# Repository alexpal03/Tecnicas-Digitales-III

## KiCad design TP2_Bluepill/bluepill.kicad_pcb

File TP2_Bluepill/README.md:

# TODO

* CRC              [listo]
* Recepcion RS485  [listo]
* Urgente: BMP280  []
* Urgente: PWM 10KHz  []

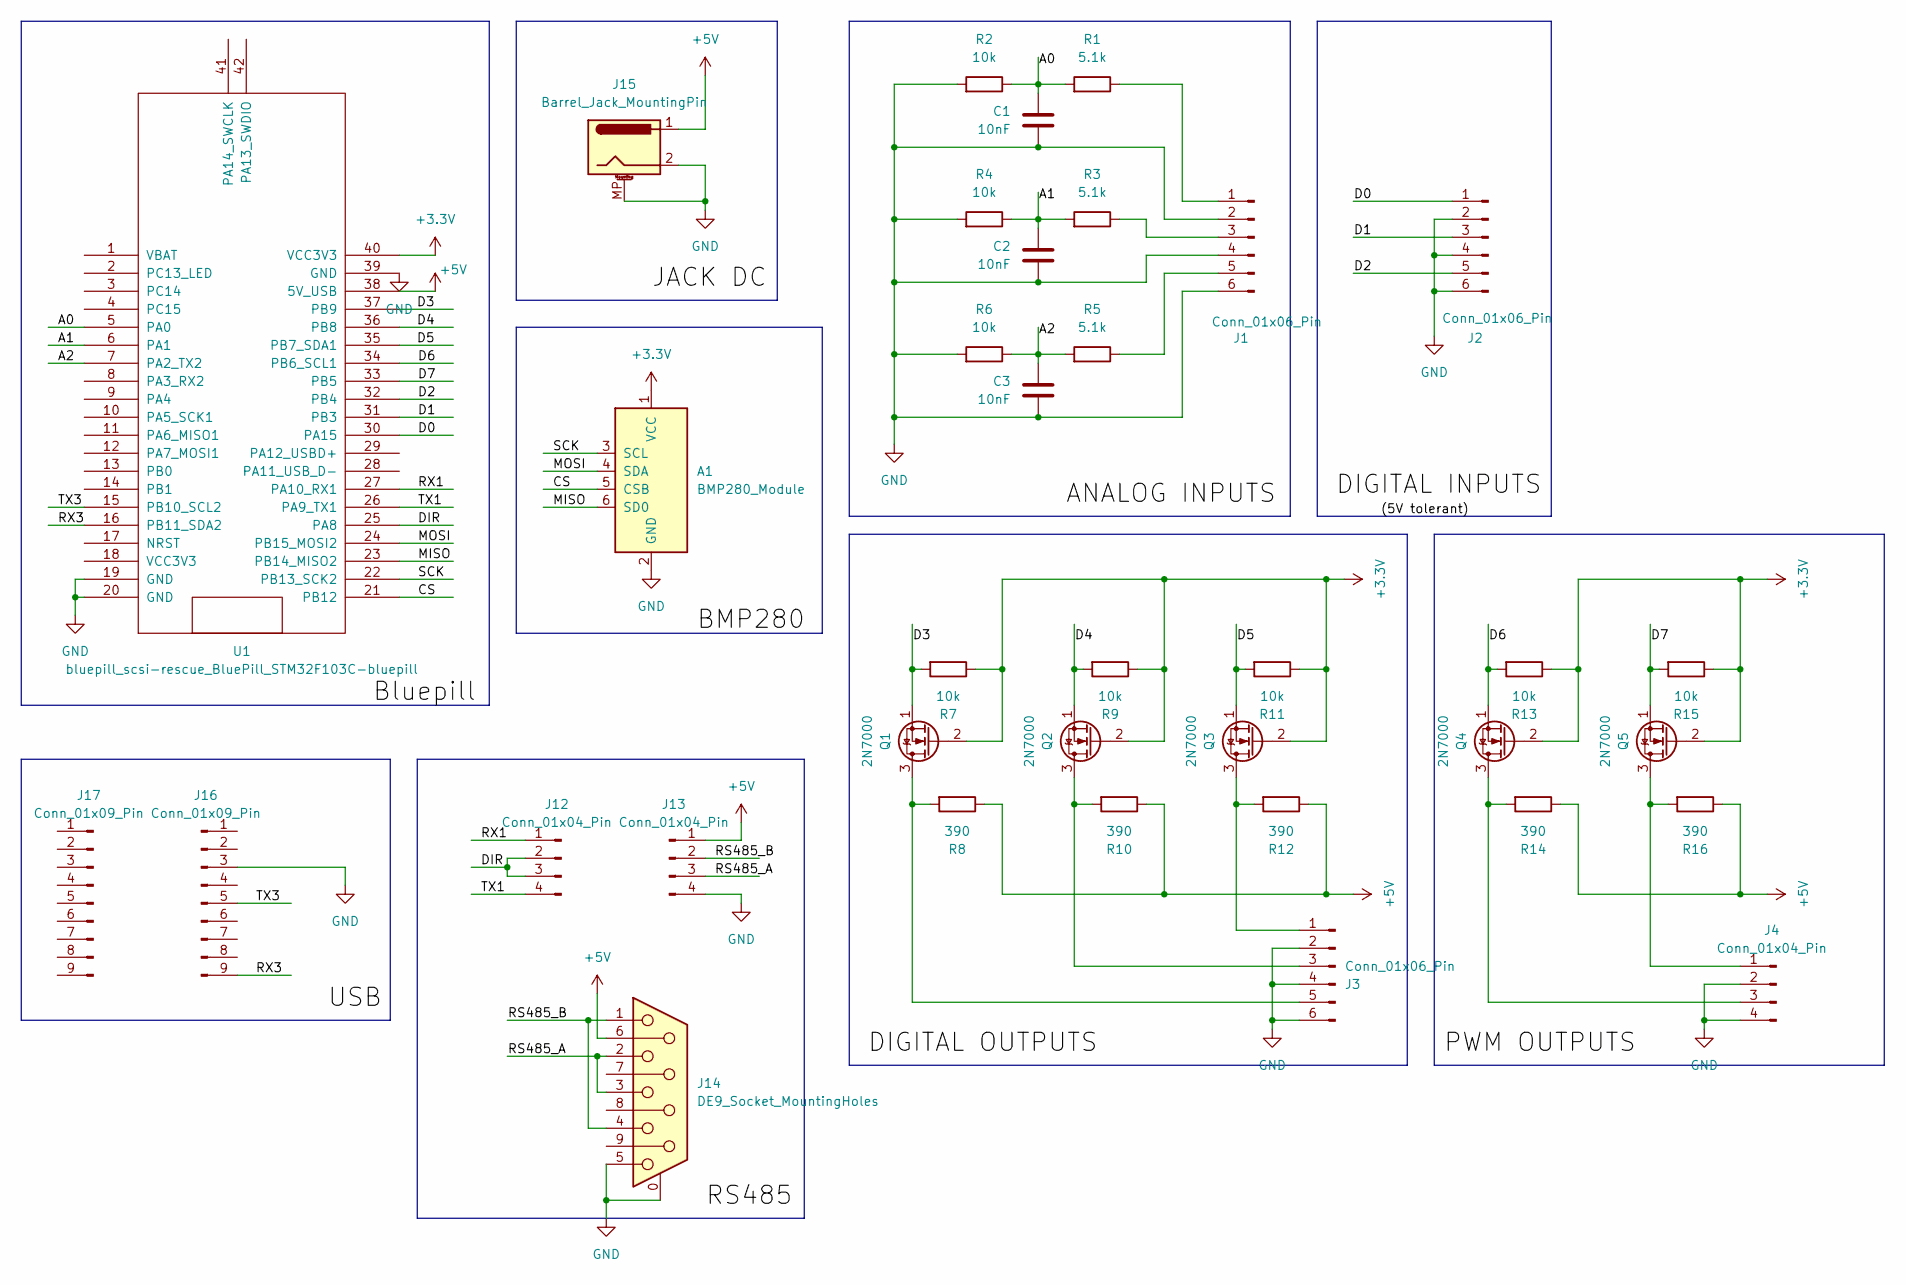
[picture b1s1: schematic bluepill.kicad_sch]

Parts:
A1: BMP280_Module
C1, C2, C3: 10nF; C_Disc_D4.3mm_W1.9mm_P5.00mm
J1, J2, J3: Conn_01x06_Pin; PhoenixContact_MSTBA_2,5_6-G_1x06_P5.00mm_Horizontal
J4: Conn_01x04_Pin; PhoenixContact_MSTBA_2,5_4-G_1x04_P5.00mm_Horizontal
J12, J13: Conn_01x04_Pin; PinHeader_1x04_P2.54mm_Vertical
J14: DE9_Socket_MountingHoles; DSUB-9_Socket_Horizontal_P2.77x2.84mm_EdgePinOffset9.90mm_H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
J15: Barrel_Jack_MountingPin; BarrelJack_Horizontal_MP
J16, J17: Conn_01x09_Pin; PinHeader_1x09_P2.54mm_Vertical
Q1, Q2, Q3, Q4, Q5: 2N7000; TO-92_Wide
R1, R3, R5: 5.1k; R_Axial_DIN0207_L6.3mm_D2.5mm_P10.16mm_Horizontal
R2, R4, R6, R7, R9, R11, R13, R15: 10k; R_Axial_DIN0207_L6.3mm_D2.5mm_P10.16mm_Horizontal
R8, R10, R12, R14, R16: 390; R_Axial_DIN0207_L6.3mm_D2.5mm_P10.16mm_Horizontal
U1: bluepill_scsi-rescue_BluePill_STM32F103C-bluepill; BluePill_STM32F103C

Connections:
+3.3V: A1.1 (VCC), Q1.2 (G), Q2.2 (G), Q3.2 (G), Q4.2 (G), Q5.2 (G), R7.1, R9.1, R11.1, R13.1, R15.1, U1.40 (VCC3V3)
+5V: J13.1, J14.6, J15.1, R8.1, R10.1, R12.1, R14.1, R16.1, U1.38 (5V_USB)
/A0: C1.1, R1.2, R2.1, U1.5 (PA0)
/A1: C2.1, R3.2, R4.1, U1.6 (PA1)
/A2: C3.1, R5.2, R6.1, U1.7 (PA2_TX2)
/CS: A1.5 (CSB), U1.21 (PB12)
/D0: J2.1, U1.30 (PA15)
/D1: J2.3, U1.31 (PB3)
/D2: J2.5, U1.32 (PB4)
/D3: Q1.1 (S), R7.2, U1.37 (PB9)
/D4: Q2.1 (S), R9.2, U1.36 (PB8)
/D5: Q3.1 (S), R11.2, U1.35 (PB7_SDA1)
/D6: Q4.1 (S), R13.2, U1.34 (PB6_SCL1)
/D7: Q5.1 (S), R15.2, U1.33 (PB5)
/DIR: J12.2, J12.3, U1.25 (PA8)
/MISO: A1.6 (SD0), U1.23 (PB14_MISO2)
/MOSI: A1.4 (SDA), U1.24 (PB15_MOSI2)
/RS485_A: J13.3, J14.2, J14.3
/RS485_B: J13.2, J14.1, J14.4
/RX1: J12.1, U1.27 (PA10_RX1)
/RX3: J16.9, U1.16 (PB11_SDA2)
/SCK: A1.3 (SCL), U1.22 (PB13_SCK2)
/TX1: J12.4, U1.26 (PA9_TX1)
/TX3: J16.5, U1.15 (PB10_SCL2)
GND: A1.2 (GND), C1.2, C2.2, C3.2, J1.2, J1.4, J1.6, J2.2, J2.4, J2.6, J3.2, J3.4, J3.6, J4.2, J4.4, J13.4, J14.0 (PAD), J14.5, J15.2, J15.MP (MountPin), J16.3, R2.2, R4.2, R6.2, U1.19 (GND), U1.20 (GND), U1.39 (GND)
unnamed: J1.1, R1.1
unnamed: J1.3, R3.1
unnamed: J1.5, R5.1
unnamed: J3.1, Q3.3 (D), R12.2
unnamed: J3.3, Q2.3 (D), R10.2
unnamed: J3.5, Q1.3 (D), R8.2
unnamed: J4.1, Q5.3 (D), R16.2
unnamed: J4.3, Q4.3 (D), R14.2

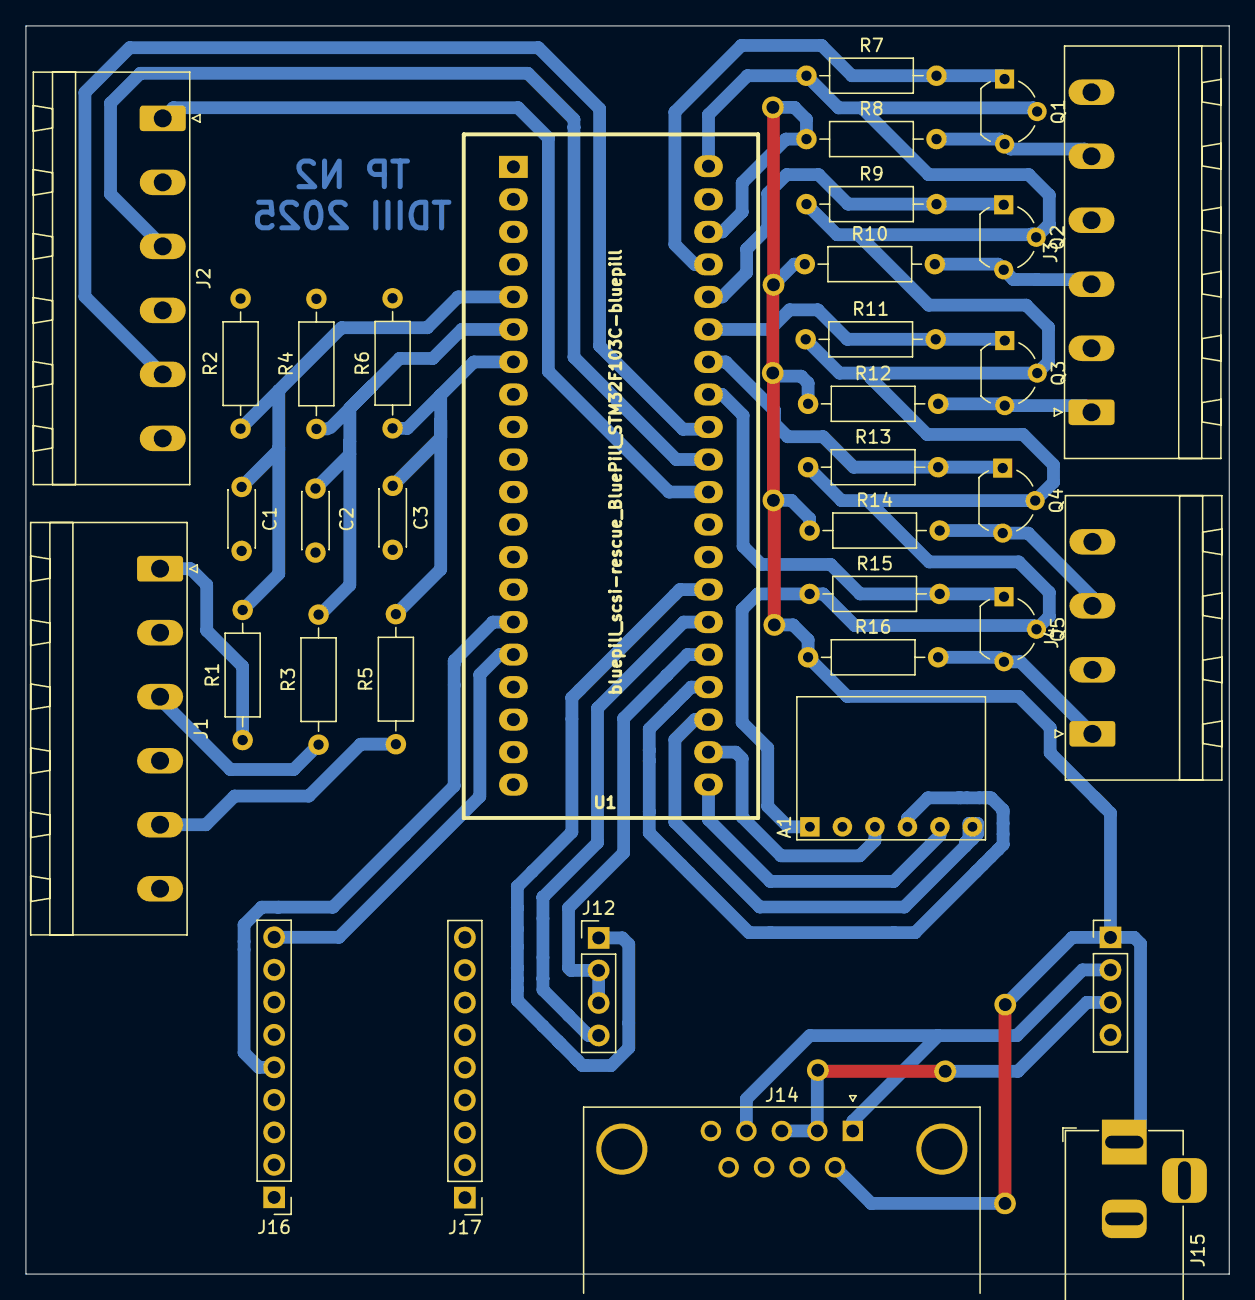
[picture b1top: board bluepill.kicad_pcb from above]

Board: 2 copper layers, 94.0 x 97.5 mm, 36 parts (0 on the bottom side), 33 nets.

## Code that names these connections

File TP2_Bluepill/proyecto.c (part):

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  /* USER CODE BEGIN 2 */

  // Inicialización timers PWM
  HAL_TIM_PWM_Start(&htim3, TIM_CHANNEL_2);  // PB5
  HAL_TIM_PWM_Start(&htim4, TIM_CHANNEL_1);  // PB6


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  /*Configure GPIO pin Output Level */
  HAL_GPIO_WritePin(GPIOA, GPIO_PIN_8, GPIO_PIN_RESET);

  /*Configure GPIO pins : PB12 PB7 PB8 PB9 */
  GPIO_InitStruct.Pin = GPIO_PIN_12|GPIO_PIN_7|GPIO_PIN_8|GPIO_PIN_9;
  GPIO_InitStruct.Mode = GPIO_MODE_OUTPUT_PP;
  GPIO_InitStruct.Pull = GPIO_NOPULL;
  GPIO_InitStruct.Speed = GPIO_SPEED_FREQ_LOW;
  HAL_GPIO_Init(GPIOB, &GPIO_InitStruct);

  /*Configure GPIO pin : PA8 */
  GPIO_InitStruct.Pin = GPIO_PIN_8;
  GPIO_InitStruct.Mode = GPIO_MODE_OUTPUT_PP;
  GPIO_InitStruct.Pull = GPIO_NOPULL;
  GPIO_InitStruct.Speed = GPIO_SPEED_FREQ_LOW;
  HAL_GPIO_Init(GPIOA, &GPIO_InitStruct);

  /*Configure GPIO pin : PA15 */
  GPIO_InitStruct.Pin = GPIO_PIN_15;
  GPIO_InitStruct.Mode = GPIO_MODE_INPUT;
  GPIO_InitStruct.Pull = GPIO_PULLDOWN;
  HAL_GPIO_Init(GPIOA, &GPIO_InitStruct);

  /*Configure GPIO pins : PB3 PB4 */
  GPIO_InitStruct.Pin = GPIO_PIN_3|GPIO_PIN_4;
  GPIO_InitStruct.Mode = GPIO_MODE_INPUT;
  GPIO_InitStruct.Pull = GPIO_PULLDOWN;
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  {

	// Lectura ADC
	uint16_t valores_adc_PA[3]; // PA0 PA1 PA2

	for (int i = 0; i < 3; i++)
	{
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			}

			// Seteo de duty cycle del PWM
			__HAL_TIM_SET_COMPARE(&htim3, TIM_CHANNEL_2, recepcion[2]); // PB5
			__HAL_TIM_SET_COMPARE(&htim4, TIM_CHANNEL_1, recepcion[3]); // PB6
		}

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
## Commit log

2025-03-28 Create PruebaCompleto
2025-03-28 Create completo_interrupciones
2025-03-28 Rename completo_interrupciones to completo_interrupciones.c
2025-03-28 Rename PruebaCompleto to PruebaCompleto.c
2025-03-28 Rename pruebaPWMreal.c to prueba_pwm_timer_funciona.c
2025-03-28 Rename completo_interrupciones.pdsprj to simu_proteus.pdsprj
2025-03-29 Create interrup_gpio_estado_funciona
2025-03-29 Rename interrupt_hard_pwm.c to interrupt_hard_pwm_funciona.c
2025-04-03 Create tx_pwm_wdt_funciona.c
    Falta hacer funciona la rx
2025-05-04 Rename 04-04-25-funciona.c to TP1_PIC12F629/04-04-25-funciona.c
2025-05-04 Rename CODIGO_FINAL.c to TP1_PIC12F629/CODIGO_FINAL.c
2025-05-04 Rename interrup_gpio_estado_funciona to TP1_PIC12F629/interrup_gpio_estado_funciona
2025-05-04 Rename interrupt_hard_funciona.c to TP1_PIC12F629/interrupt_hard_funciona.c
2025-05-04 Rename interrupt_hard_pwm_funciona.c to TP1_PIC12F629/interrupt_hard_pwm_funciona.c
2025-05-04 Rename interrupt_pwm_wdt_funciona.c to TP1_PIC12F629/interrupt_pwm_wdt_funciona.c
2025-05-04 Rename prueba_pwm_timer_funciona.c to TP1_PIC12F629/prueba_pwm_timer_funciona.c
2025-05-04 Rename simu_proteus.pdsprj to TP1_PIC12F629/simu_proteus.pdsprj
2025-05-04 Rename tx_pwm_wdt_funciona.c to TP1_PIC12F629/tx_pwm_wdt_funciona.c
2025-05-17 Create code
2025-05-19 Rename code to main.c
2025-06-06 Rename main.c to proyecto.c

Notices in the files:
TP2_Bluepill/proyecto.c:
© Copyright (c) 2025 STMicroelectronics.
All rights reserved.
This software component is licensed by ST under BSD 3-Clause license,
the "License"; You may not use this file except in compliance with the
License. You may obtain a copy of the License at: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
